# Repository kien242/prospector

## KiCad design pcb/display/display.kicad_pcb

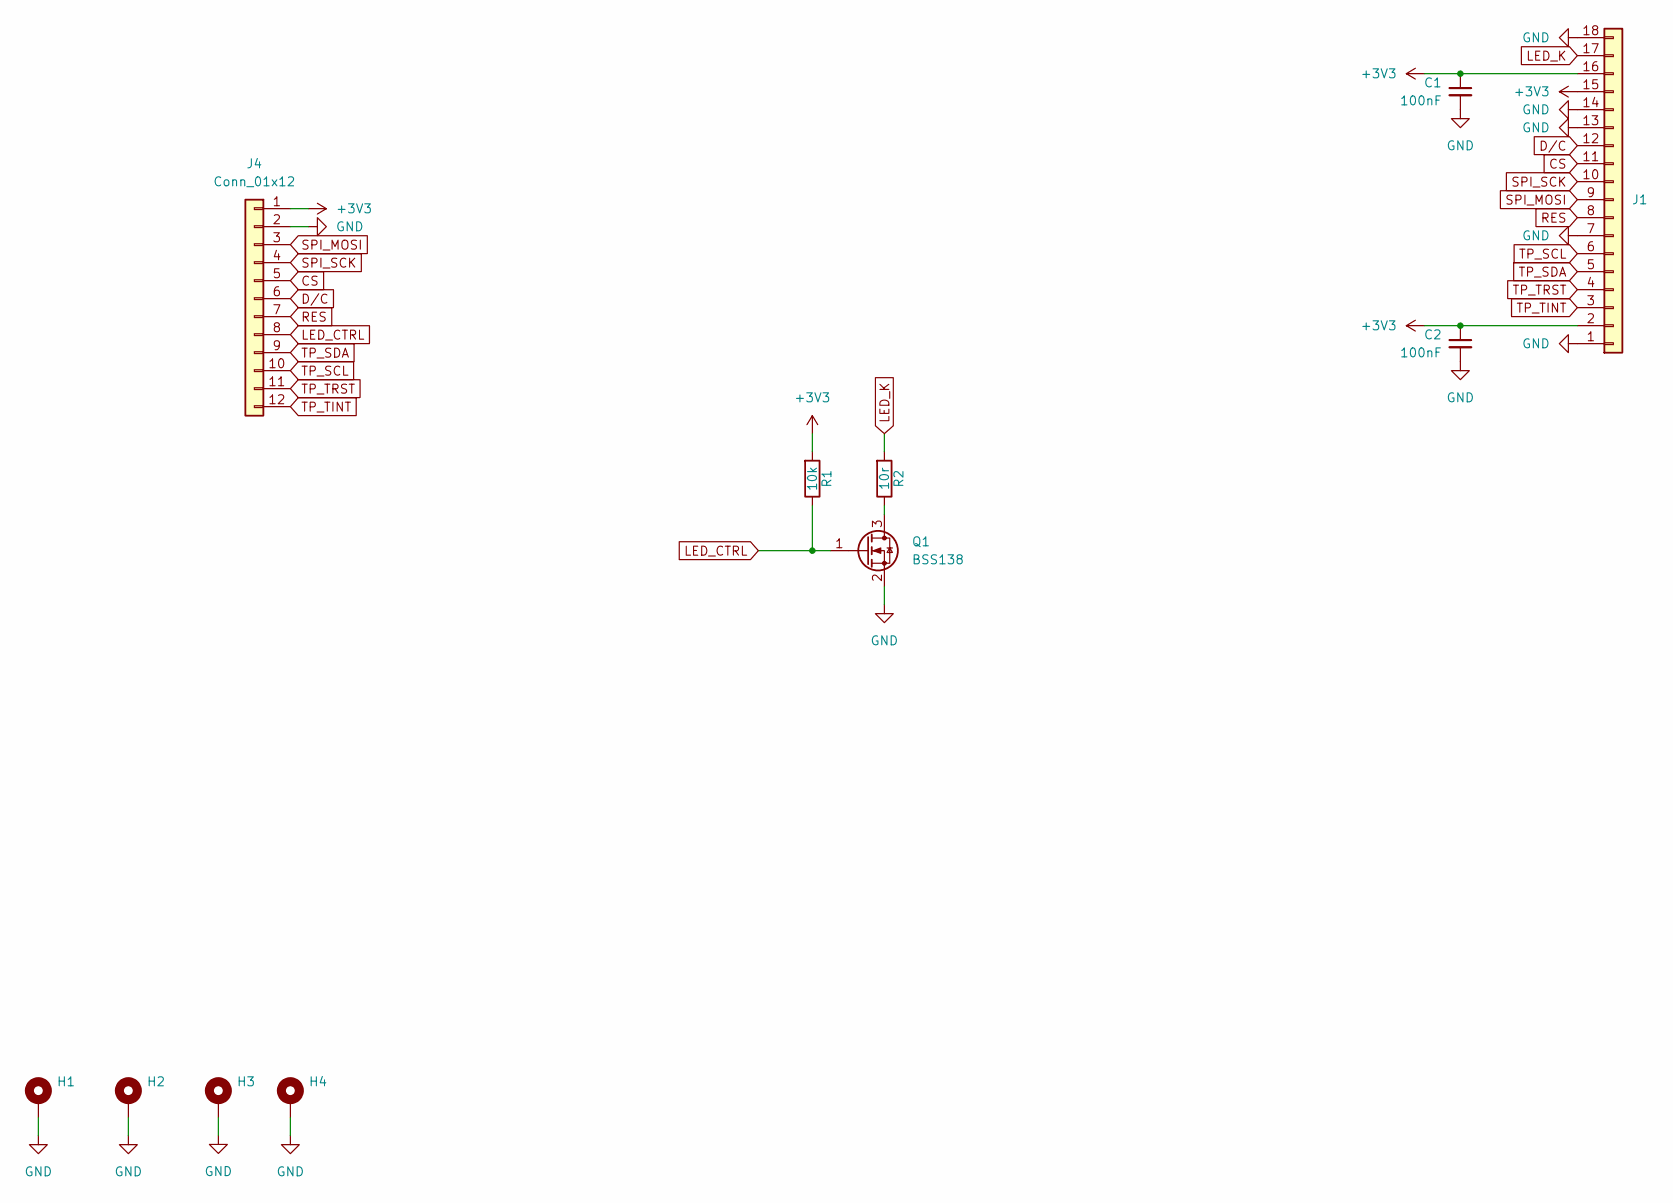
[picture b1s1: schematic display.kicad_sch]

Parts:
C1, C2: 100nF; C_0603_1608Metric_Pad1.08x0.95mm_HandSolder
H1, H2, H3, H4: MountingHole_2.7mm_M2.5_DIN965_Pad
J1: Hirose_FH12-18S-0.5SH_1x18-1MP_P0.50mm_Horizontal
J4: Conn_01x12; Hirose_FH12-12S-0.5SH_1x12-1MP_P0.50mm_Horizontal
Q1: BSS138; SOT-23_Handsoldering
R1: 10k; R_0603_1608Metric_Pad0.98x0.95mm_HandSolder
R2: 10r; R_0603_1608Metric_Pad0.98x0.95mm_HandSolder

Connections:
+3V3: C1.1, C2.1, J1.2, J1.15, J1.16, J4.1, R1.2
CS: J1.11, J4.5
D/C: J1.12, J4.6
GND: C1.2, C2.2, H1.1, H2.1, H3.1, H4.1, J1.1, J1.7, J1.13, J1.14, J1.18, J4.2, Q1.2 (S)
LED_CTRL: J4.8, Q1.1 (G), R1.1
LED_K: J1.17, R2.2
unnamed: Q1.3 (D), R2.1
RES: J1.8, J4.7
SPI_MOSI: J1.9, J4.3
SPI_SCK: J1.10, J4.4
TP_SCL: J1.6, J4.10
TP_SDA: J1.5, J4.9
TP_TINT: J1.3, J4.12
TP_TRST: J1.4, J4.11

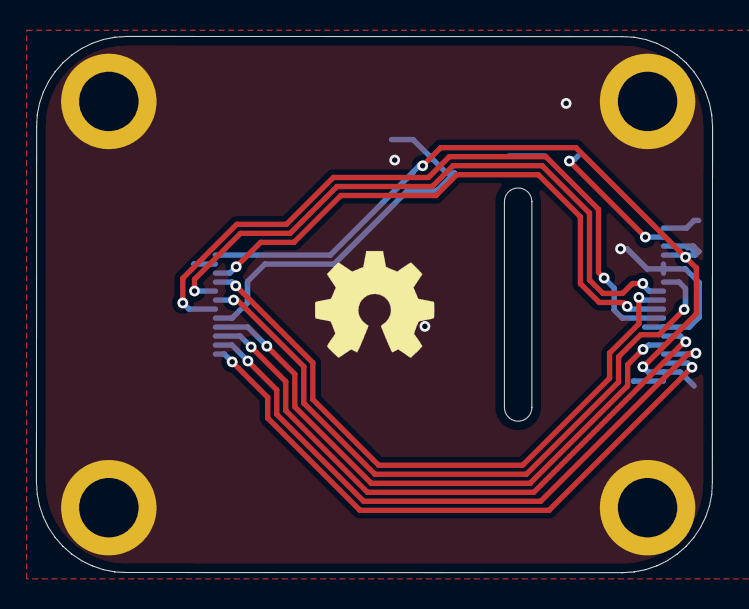
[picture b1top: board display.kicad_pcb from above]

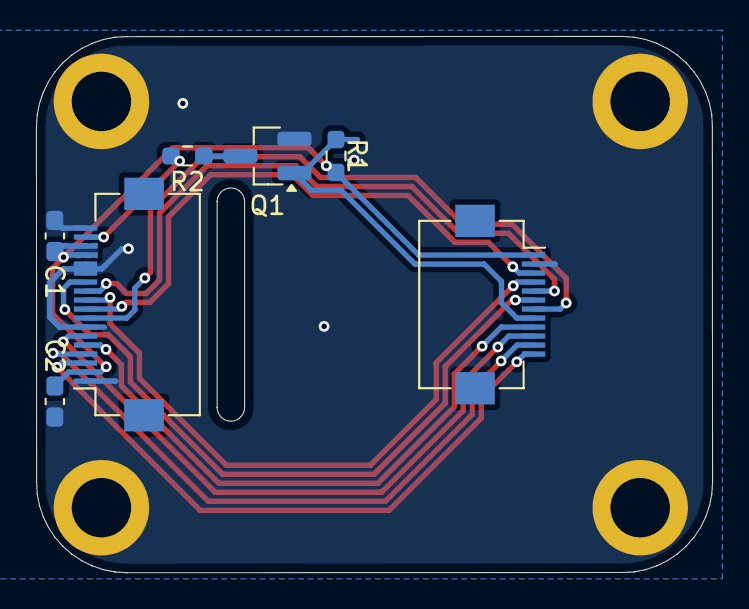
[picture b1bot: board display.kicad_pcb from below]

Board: 2 copper layers, 37.6 x 29.8 mm, 11 parts (11 on the bottom side), 14 nets.

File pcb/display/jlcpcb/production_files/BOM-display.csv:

Comment,Designator,Footprint,LCSC,Quantity
Conn_01x12,J4,Hirose_FH12-12S-0.5SH_1x12-1MP_P0.50mm_Horizontal,,1
10r,R2,R_0603_1608Metric_Pad0.98x0.95mm_HandSolder,,1
100nF,C1,C_0603_1608Metric_Pad1.08x0.95mm_HandSolder,,1
100nF,C2,C_0603_1608Metric_Pad1.08x0.95mm_HandSolder,,1
~,J1,Hirose_FH12-18S-0.5SH_1x18-1MP_P0.50mm_Horizontal,,1
10k,R1,R_0603_1608Metric_Pad0.98x0.95mm_HandSolder,,1
BSS138,Q1,SOT-23_Handsoldering,,1

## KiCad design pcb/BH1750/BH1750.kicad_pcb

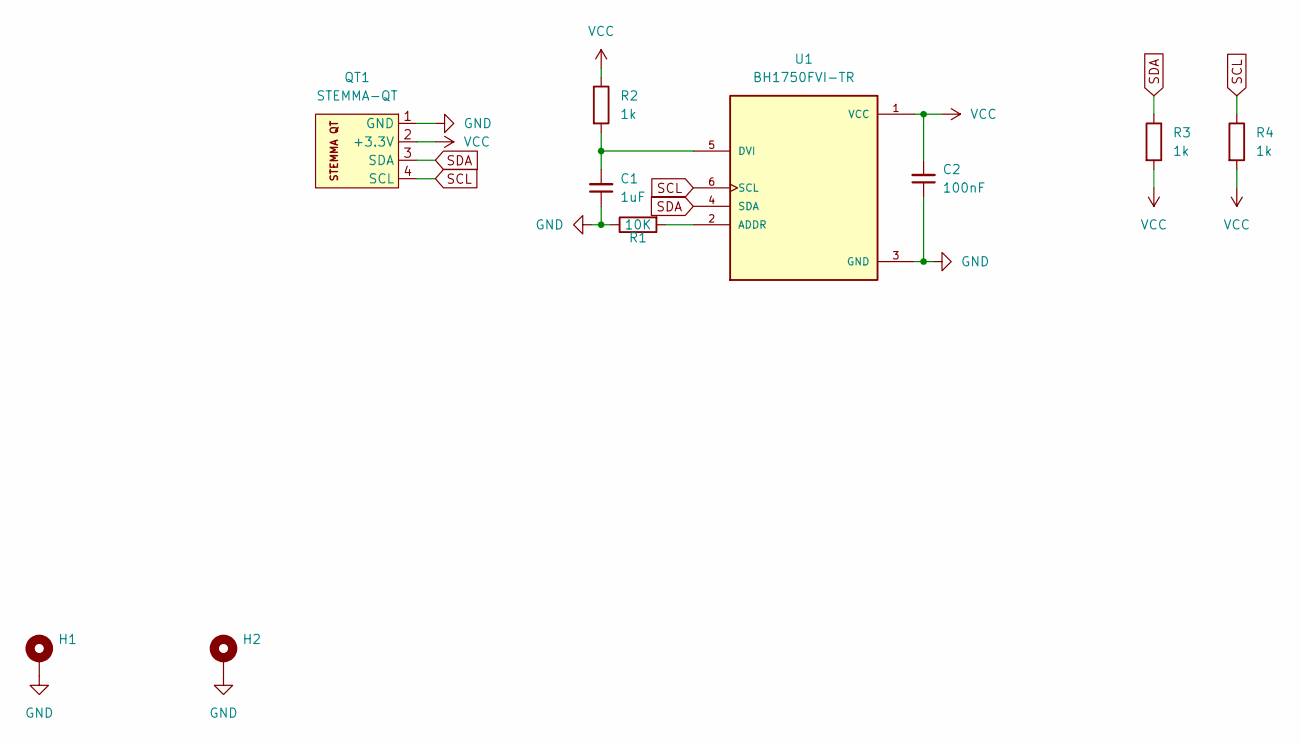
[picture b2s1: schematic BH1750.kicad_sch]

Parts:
C1: 1uF; C_0603_1608Metric_Pad1.08x0.95mm_HandSolder
C2: 100nF; C_0603_1608Metric_Pad1.08x0.95mm_HandSolder
H1, H2: MountingHole_2.2mm_M2_DIN965_Pad
QT1: STEMMA-QT; Stemma-QT
R1: 10K; R_0603_1608Metric_Pad0.98x0.95mm_HandSolder
R2, R3, R4: 1k; R_0603_1608Metric_Pad0.98x0.95mm_HandSolder
U1: BH1750FVI-TR; XDCR_BH1750FVI-TR; PARTREV D

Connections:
GND: C1.1, C2.1, H1.1, H2.1, QT1.1 (GND), R1.1, U1.3 (GND)
unnamed: R1.2, U1.2 (ADDR)
unnamed: C1.2, R2.2, U1.5 (DVI)
SCL: QT1.4 (SCL), R4.1, U1.6 (SCL)
SDA: QT1.3 (SDA), R3.1, U1.4 (SDA)
VCC: C2.2, QT1.2 (+3.3V), R2.1, R3.2, R4.2, U1.1 (VCC)

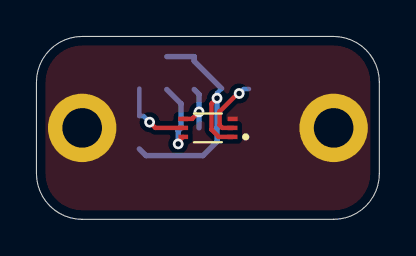
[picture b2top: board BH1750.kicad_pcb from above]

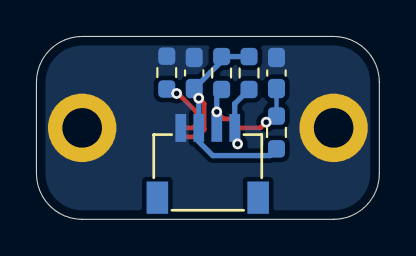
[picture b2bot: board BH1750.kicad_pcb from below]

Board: 2 copper layers, 19.0 x 10.2 mm, 10 parts (7 on the bottom side), 6 nets.

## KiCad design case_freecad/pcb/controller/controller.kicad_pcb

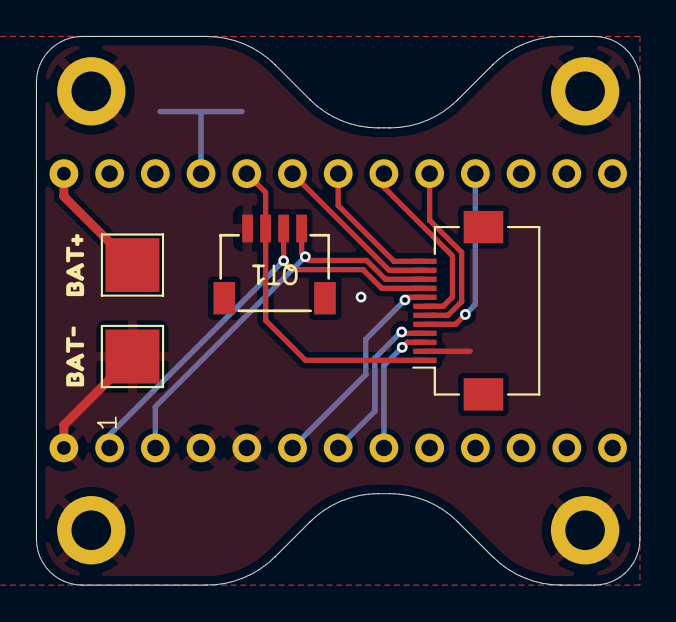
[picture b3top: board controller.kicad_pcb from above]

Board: 2 copper layers, 33.5 x 30.5 mm, 12 parts (1 on the bottom side), 14 nets.

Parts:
H1, H2, H3, H4: MountingHole_2.2mm_M2_DIN965_Pad
J4: Conn_01x12; Hirose_FH12-12S-0.5SH_1x12-1MP_P0.50mm_Horizontal
QT1: STEMMA-QT; Stemma-QT
SW1: SW_Push; Button_3x4x2.5
TP1, TP2: TestPoint_Pad_3.0x3.0mm
U2: nice_nano; Nice!nano_NRF52840
kibuzzard-6919562A: G***; kibuzzard-6919562A
kibuzzard-69195637: G***; kibuzzard-69195637

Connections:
CS: J4.5, U2.16 (P1.13)
D/C: J4.6, U2.17 (P1.15)
GND: H1.1, H2.1, H3.1, H4.1, J4.2, QT1.1 (GND), SW1.2, TP2.1, U2.3 (GND), U2.4 (GND), U2.28 (BAT-)
I2C_SCL: J4.10, QT1.4 (SCL), U2.2 (RX1/P0.08)
I2C_SDA: J4.9, QT1.3 (SDA), U2.1 (TX0/P0.06)
LED_CTRL: J4.8, U2.5 (P0.17)
unnamed: TP1.1, U2.29 (BAT+)
unnamed: SW1.1, U2.22 (RST)
RES: J4.7, U2.18 (AIN0/P0.02)
SPI_MOSI: J4.3, U2.7 (P0.22)
SPI_SCK: J4.4, U2.6 (P0.20)
TP_TINT: J4.12, U2.19 (AIN5/P0.29)
TP_TRST: J4.11, U2.20 (AIN7/P0.31)
VCC: J4.1, QT1.2 (+3.3V), U2.21 (VCC)
